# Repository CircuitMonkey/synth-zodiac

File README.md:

# synth-zodiac
Zodiac themed analog synthesizer, shaped like a Dodecahedron.

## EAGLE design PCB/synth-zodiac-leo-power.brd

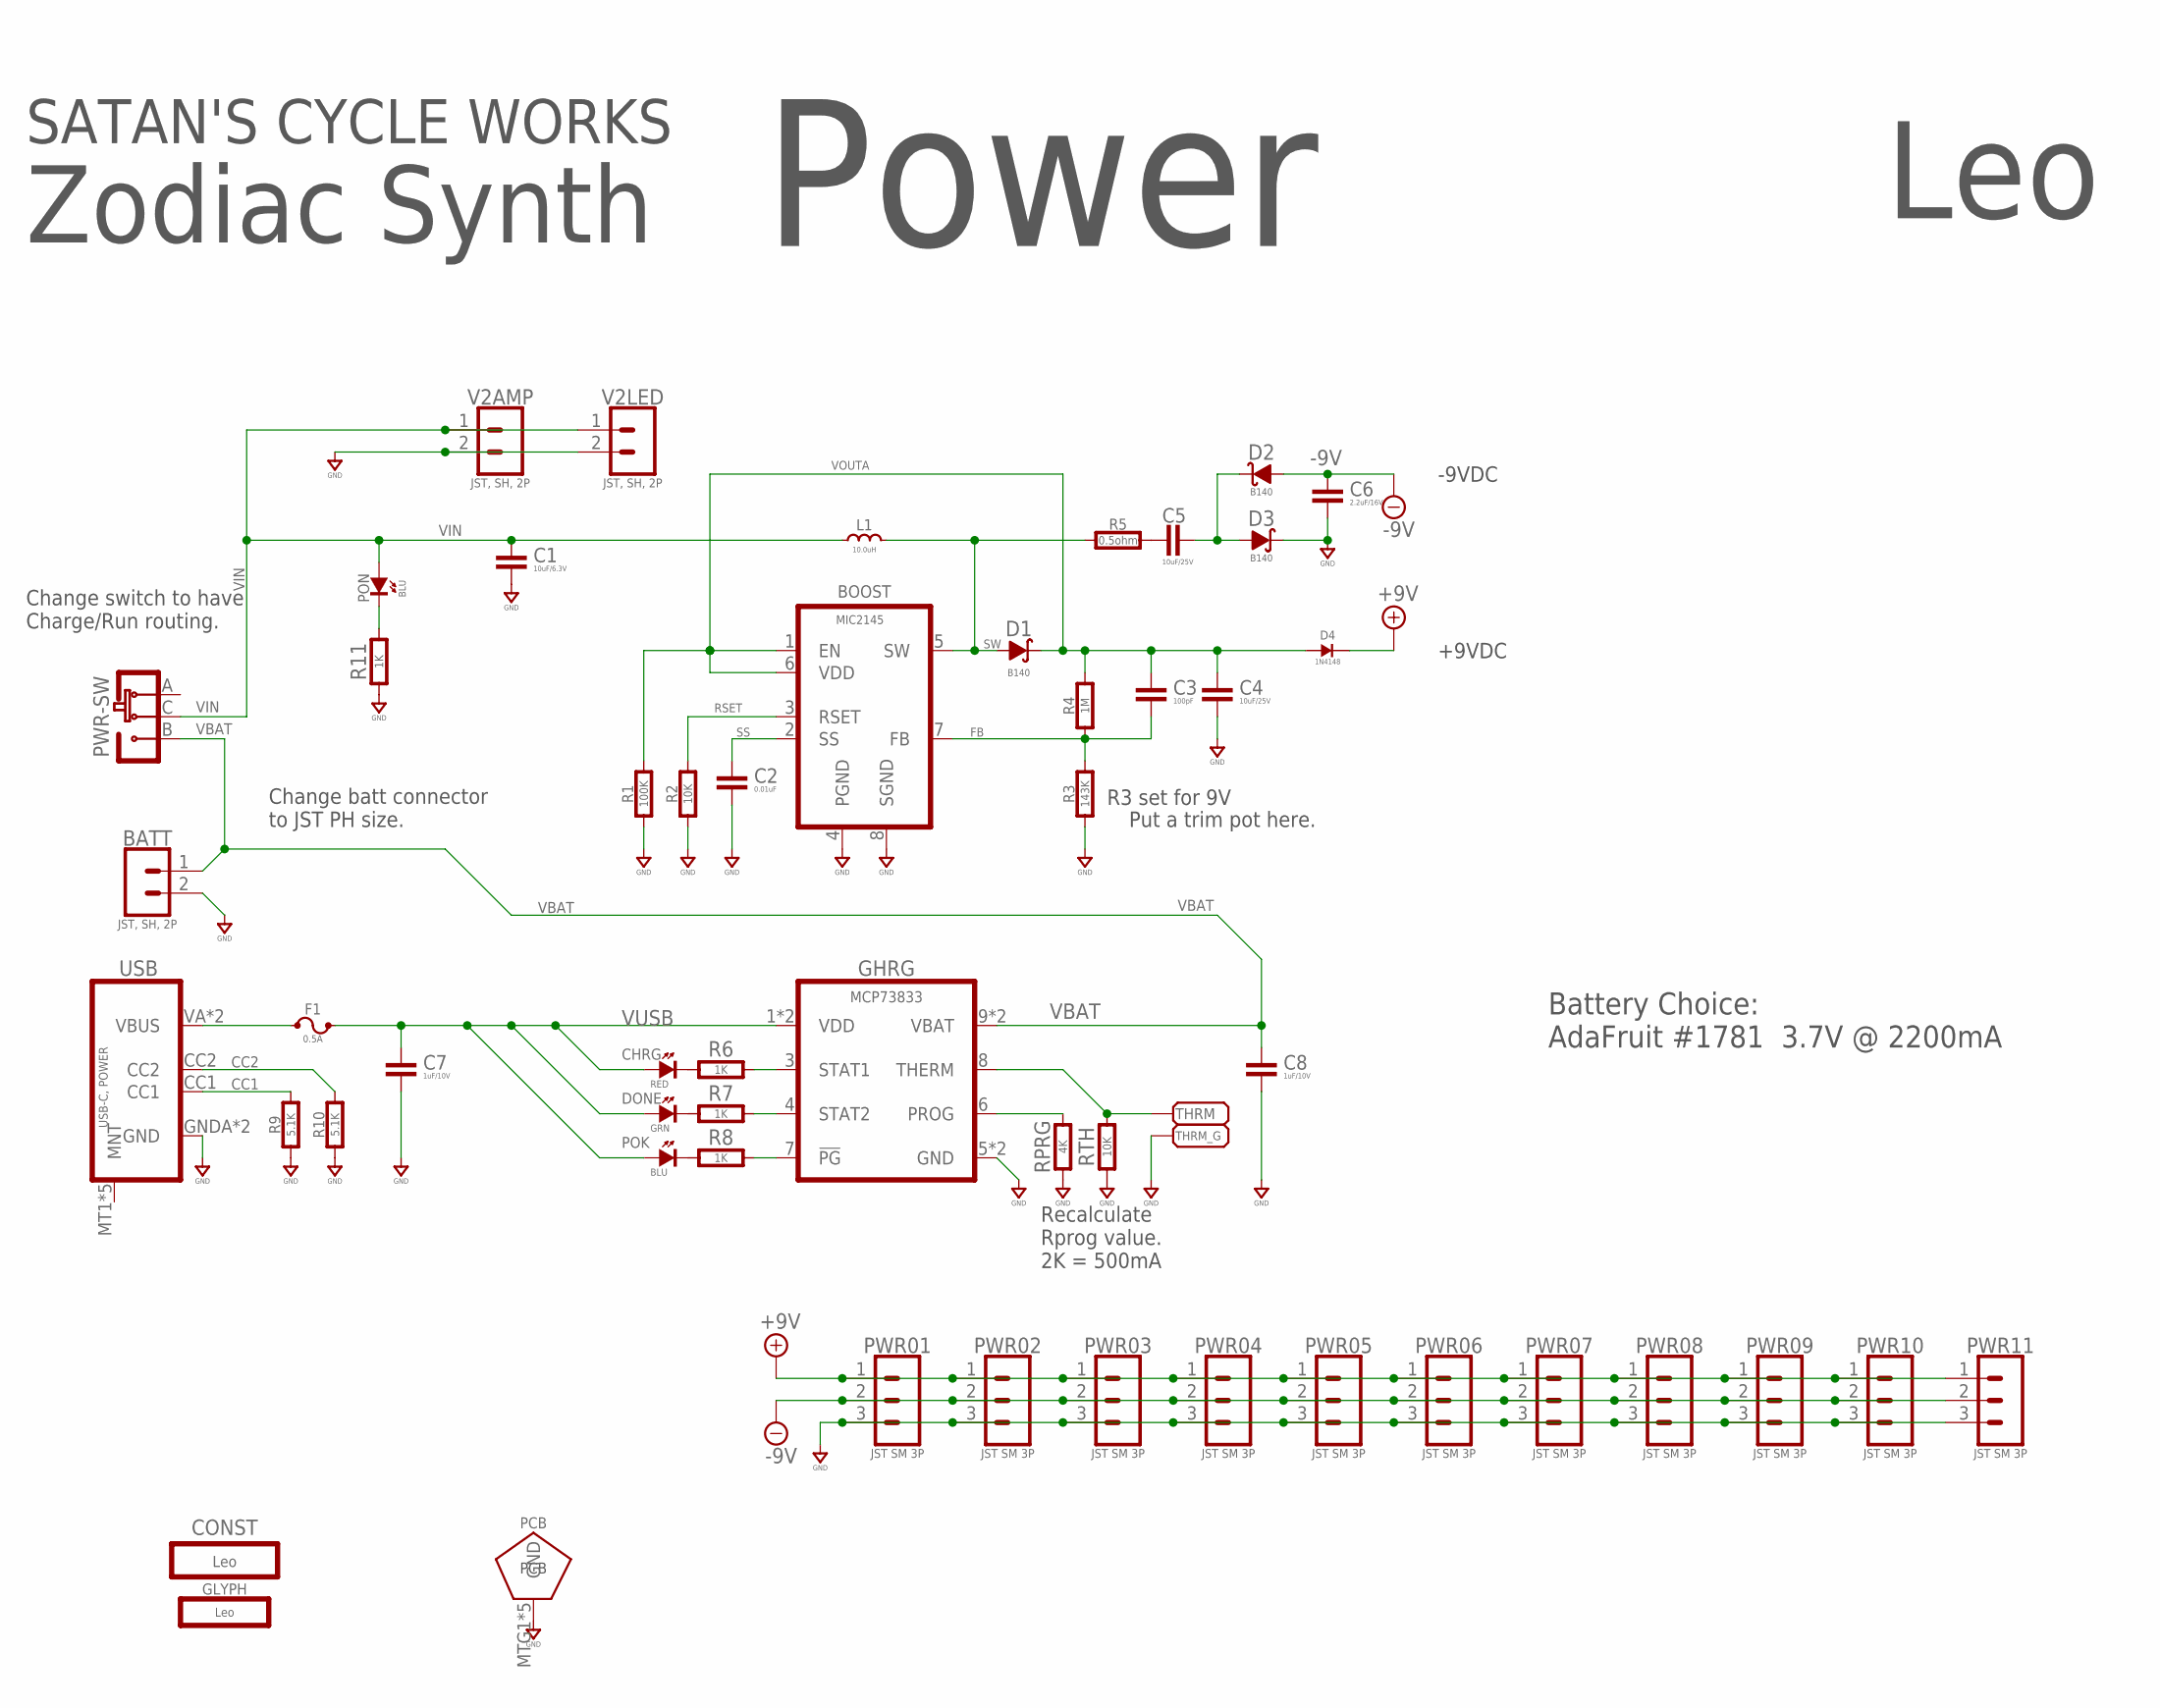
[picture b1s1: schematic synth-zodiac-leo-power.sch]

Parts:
BATT: JST, SH, 2P; BM02B-SRSS-TB
BOOST: MIC2145; MSOP8-0.65
C1: 10uF/6.3V; 0603-CAP
C2: 0.01uF; 0603-CAP
C3: 100pF; 0603-CAP
C4, C5: 10uF/25V; 0603-CAP
C6: 2.2uF/16V; 0603-CAP
C7, C8: 1uF/10V; 0603-CAP
CHRG: RED; SMD_0603
CONST: Leo; LEO-CONST
D1, D2, D3: B140; SMA
D4: 1N4148; SOD-123
DONE: GRN; SMD_0603
F1: 0.5A; BOURNS-MF-MSMF
GHRG: MCP73833; DFN-10-3X3
GLYPH: Leo; LEO-GLYPH
L1: 10.0uH; IND-SRN5040
PCB: PCB FAB; PENTAGON-40MM-RAD
POK: BLU; SMD_0603
PON: BLU; SMD_0603
PWR: SLIDE-SPDT-MNTSS-12-F45-TH-PCB-2; SS-12-F45-PNL-SMT-2
PWR01, PWR02, PWR03, PWR04, PWR05, PWR06, PWR07, PWR08, PWR09, PWR10, PWR11: JST SM 3P; BM03B-SRSS-TB
R1: 100K; 0603-RES
R2: 10K; 0603-RES
R3: 143K; 0603-RES
R4: 1M; 0603-RES
R5: 0.5ohm; 0603-RES
R6, R7, R8, R11: 1K; 0603-RES
R9, R10: 5.1K; 0603-RES
RPRG: 4K; 0603-RES
RTH: 10K; 0603-RES
THRM: PADSMD-050X050; SMD-050X050
THRM_G: PADSMD-050X050; SMD-050X050
USB: USB-C, POWER; GCT-USB4515-PANEL
V2AMP, V2LED: JST, SH, 2P; BM02B-SRSS-TB

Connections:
+9V: D4.K, PWR01.1, PWR02.1, PWR03.1, PWR04.1, PWR05.1, PWR06.1, PWR07.1, PWR08.1, PWR09.1, PWR10.1, PWR11.1
-9V: C6.1, D2.A, PWR01.2, PWR02.2, PWR03.2, PWR04.2, PWR05.2, PWR06.2, PWR07.2, PWR08.2, PWR09.2, PWR10.2, PWR11.2
CC1: R9.2, USB.CC1
CC2: R10.2, USB.CC2
FB: BOOST.7 (FB), C3.2, R3.2, R4.1
GND: BATT.2, BOOST.4 (PGND), BOOST.8 (SGND), C1.2, C2.2, C4.2, C6.2, C7.2, C8.2, D3.K, GHRG.5 (GND), GHRG.PAD (GND), PCB.MTG1, PCB.MTG2, PCB.MTG3, PCB.MTG4, PCB.MTG5, PWR01.3, PWR02.3, PWR03.3, PWR04.3, PWR05.3, PWR06.3, PWR07.3, PWR08.3, PWR09.3, PWR10.3, PWR11.3, R1.1, R2.1, R3.1, R9.1, R10.1, R11.1, RPRG.1, RTH.1, THRM_G.1, USB.GNDA (GND), USB.GNDB (GND), V2AMP.2, V2LED.2
unnamed: C5.1, R5.2
unnamed: C5.2, D2.K, D3.A
unnamed: CHRG.K (C), R6.1
unnamed: PON.K (C), R11.2
unnamed: DONE.K (C), R7.1
unnamed: POK.K (C), R8.1
unnamed: GHRG.6 (PROG), RPRG.2
unnamed: GHRG.3 (STAT1), R6.2
unnamed: GHRG.4 (STAT2), R7.2
unnamed: GHRG.7 (!PG), R8.2
unnamed: GHRG.8 (THERM), RTH.2, THRM.1
RSET: BOOST.3 (RSET), R2.2
SS: BOOST.2 (SS), C2.1
SW: BOOST.5 (SW), D1.A, L1.1, R5.1
VBAT: BATT.1, C8.1, GHRG.9 (VBAT), GHRG.10 (VBAT), PWR.B
VBUS: F1.1, USB.VA (VBUS), USB.VB (VBUS)
VIN: C1.1, L1.2, PON.A, PWR.C, V2AMP.1, V2LED.1
VOUTA: BOOST.1 (EN), BOOST.6 (VDD), C3.1, C4.1, D1.K, D4.A, R1.2, R4.2
VUSB: C7.1, CHRG.A, DONE.A, F1.2, GHRG.1 (VDD), GHRG.2 (VDD), POK.A

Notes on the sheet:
Battery Choice: AdaFruit #1781 3.7V @ 2200mA
R3 set for 9V
-9VDC
+9VDC
Put a trim pot here.
Recalculate Rprog value. 2K = 500mA
Power
Zodiac Synth
Leo
SATAN'S CYCLE WORKS
Change switch to have Charge/Run routing.
Change batt connector to JST PH size.

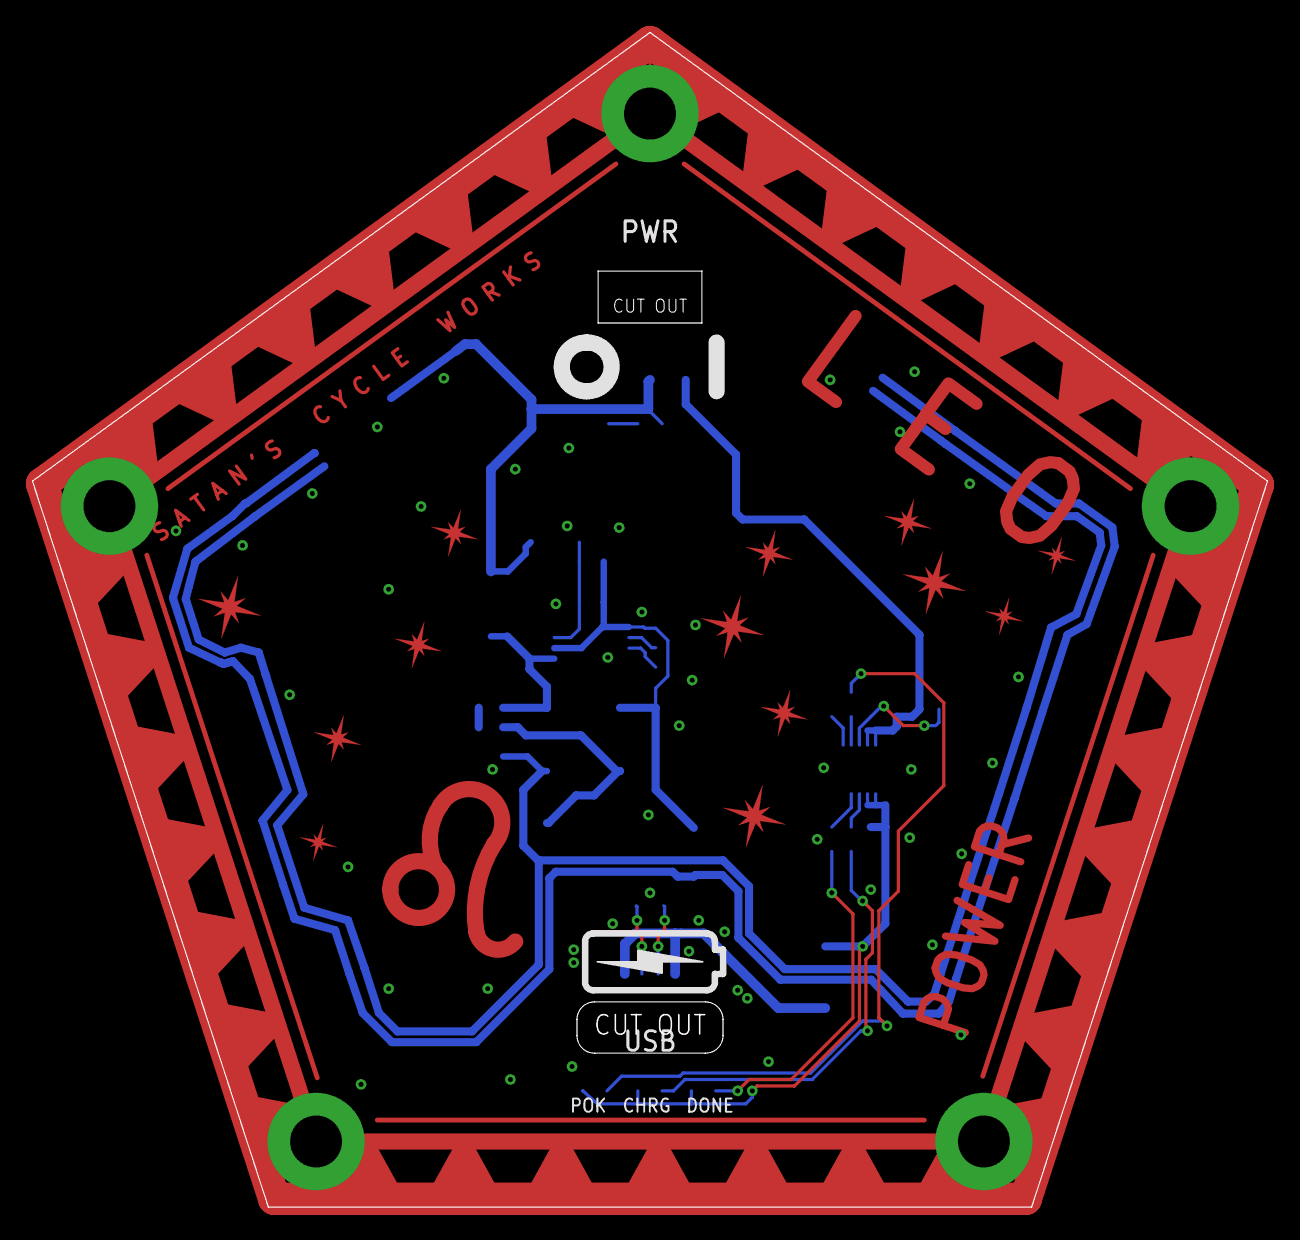
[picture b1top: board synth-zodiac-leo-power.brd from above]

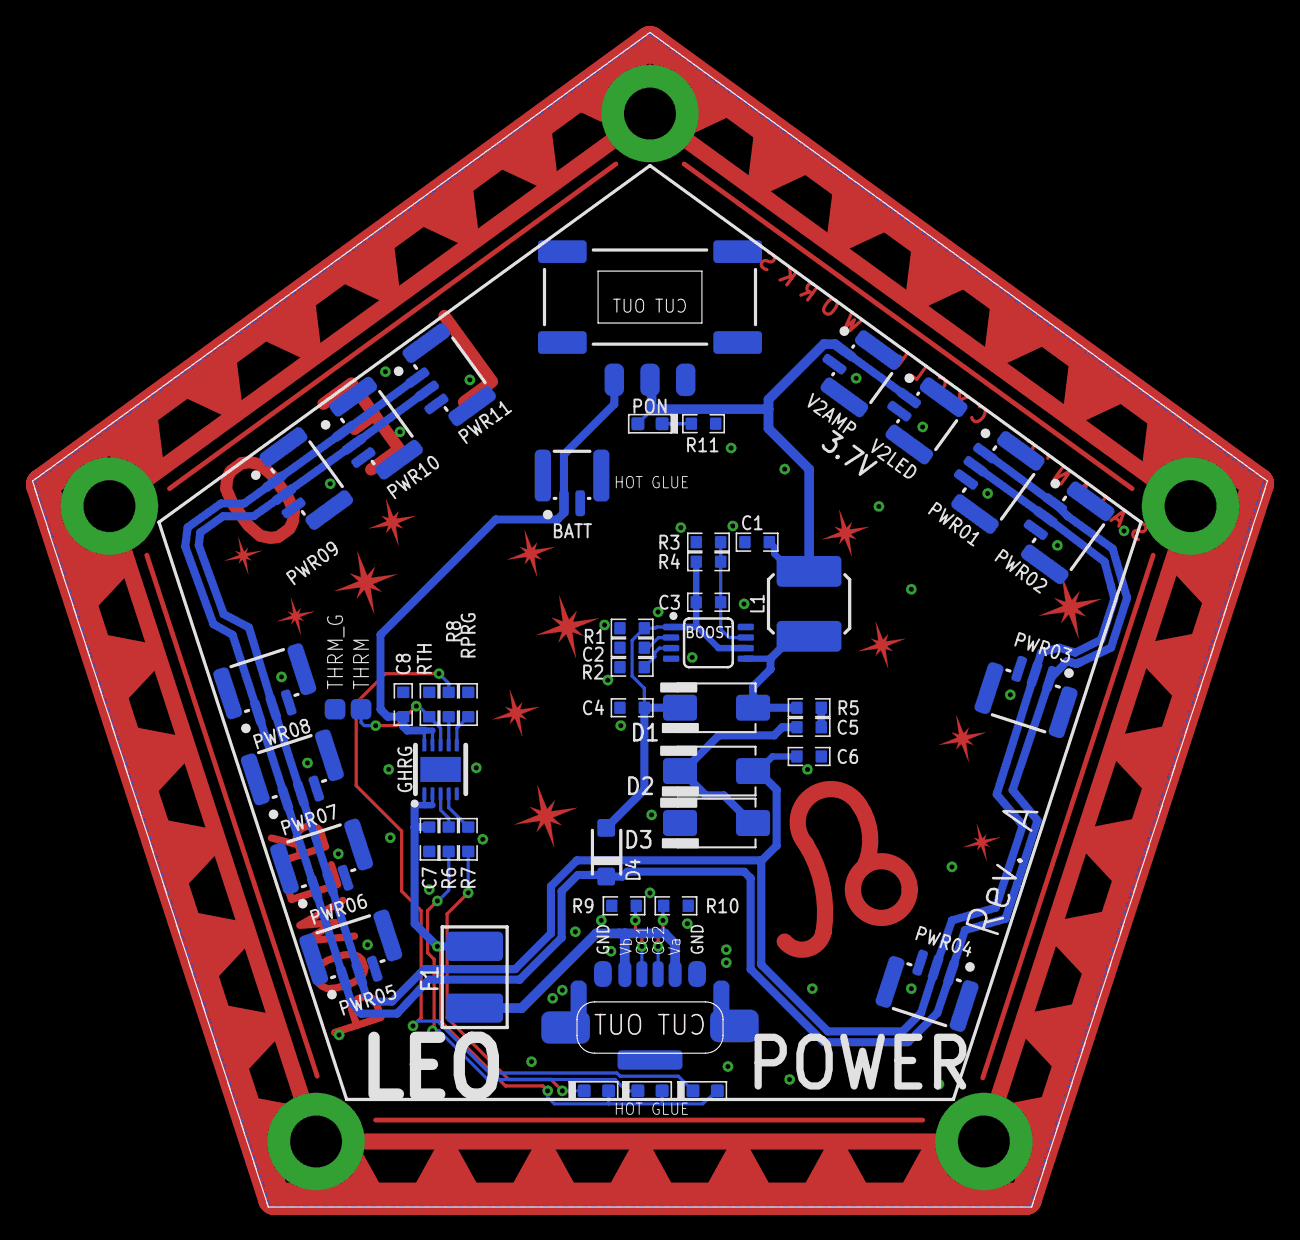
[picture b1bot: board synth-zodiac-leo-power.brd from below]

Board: 2 copper layers, 76.1 x 72.3 mm, 54 parts (49 on the bottom side), 25 nets.

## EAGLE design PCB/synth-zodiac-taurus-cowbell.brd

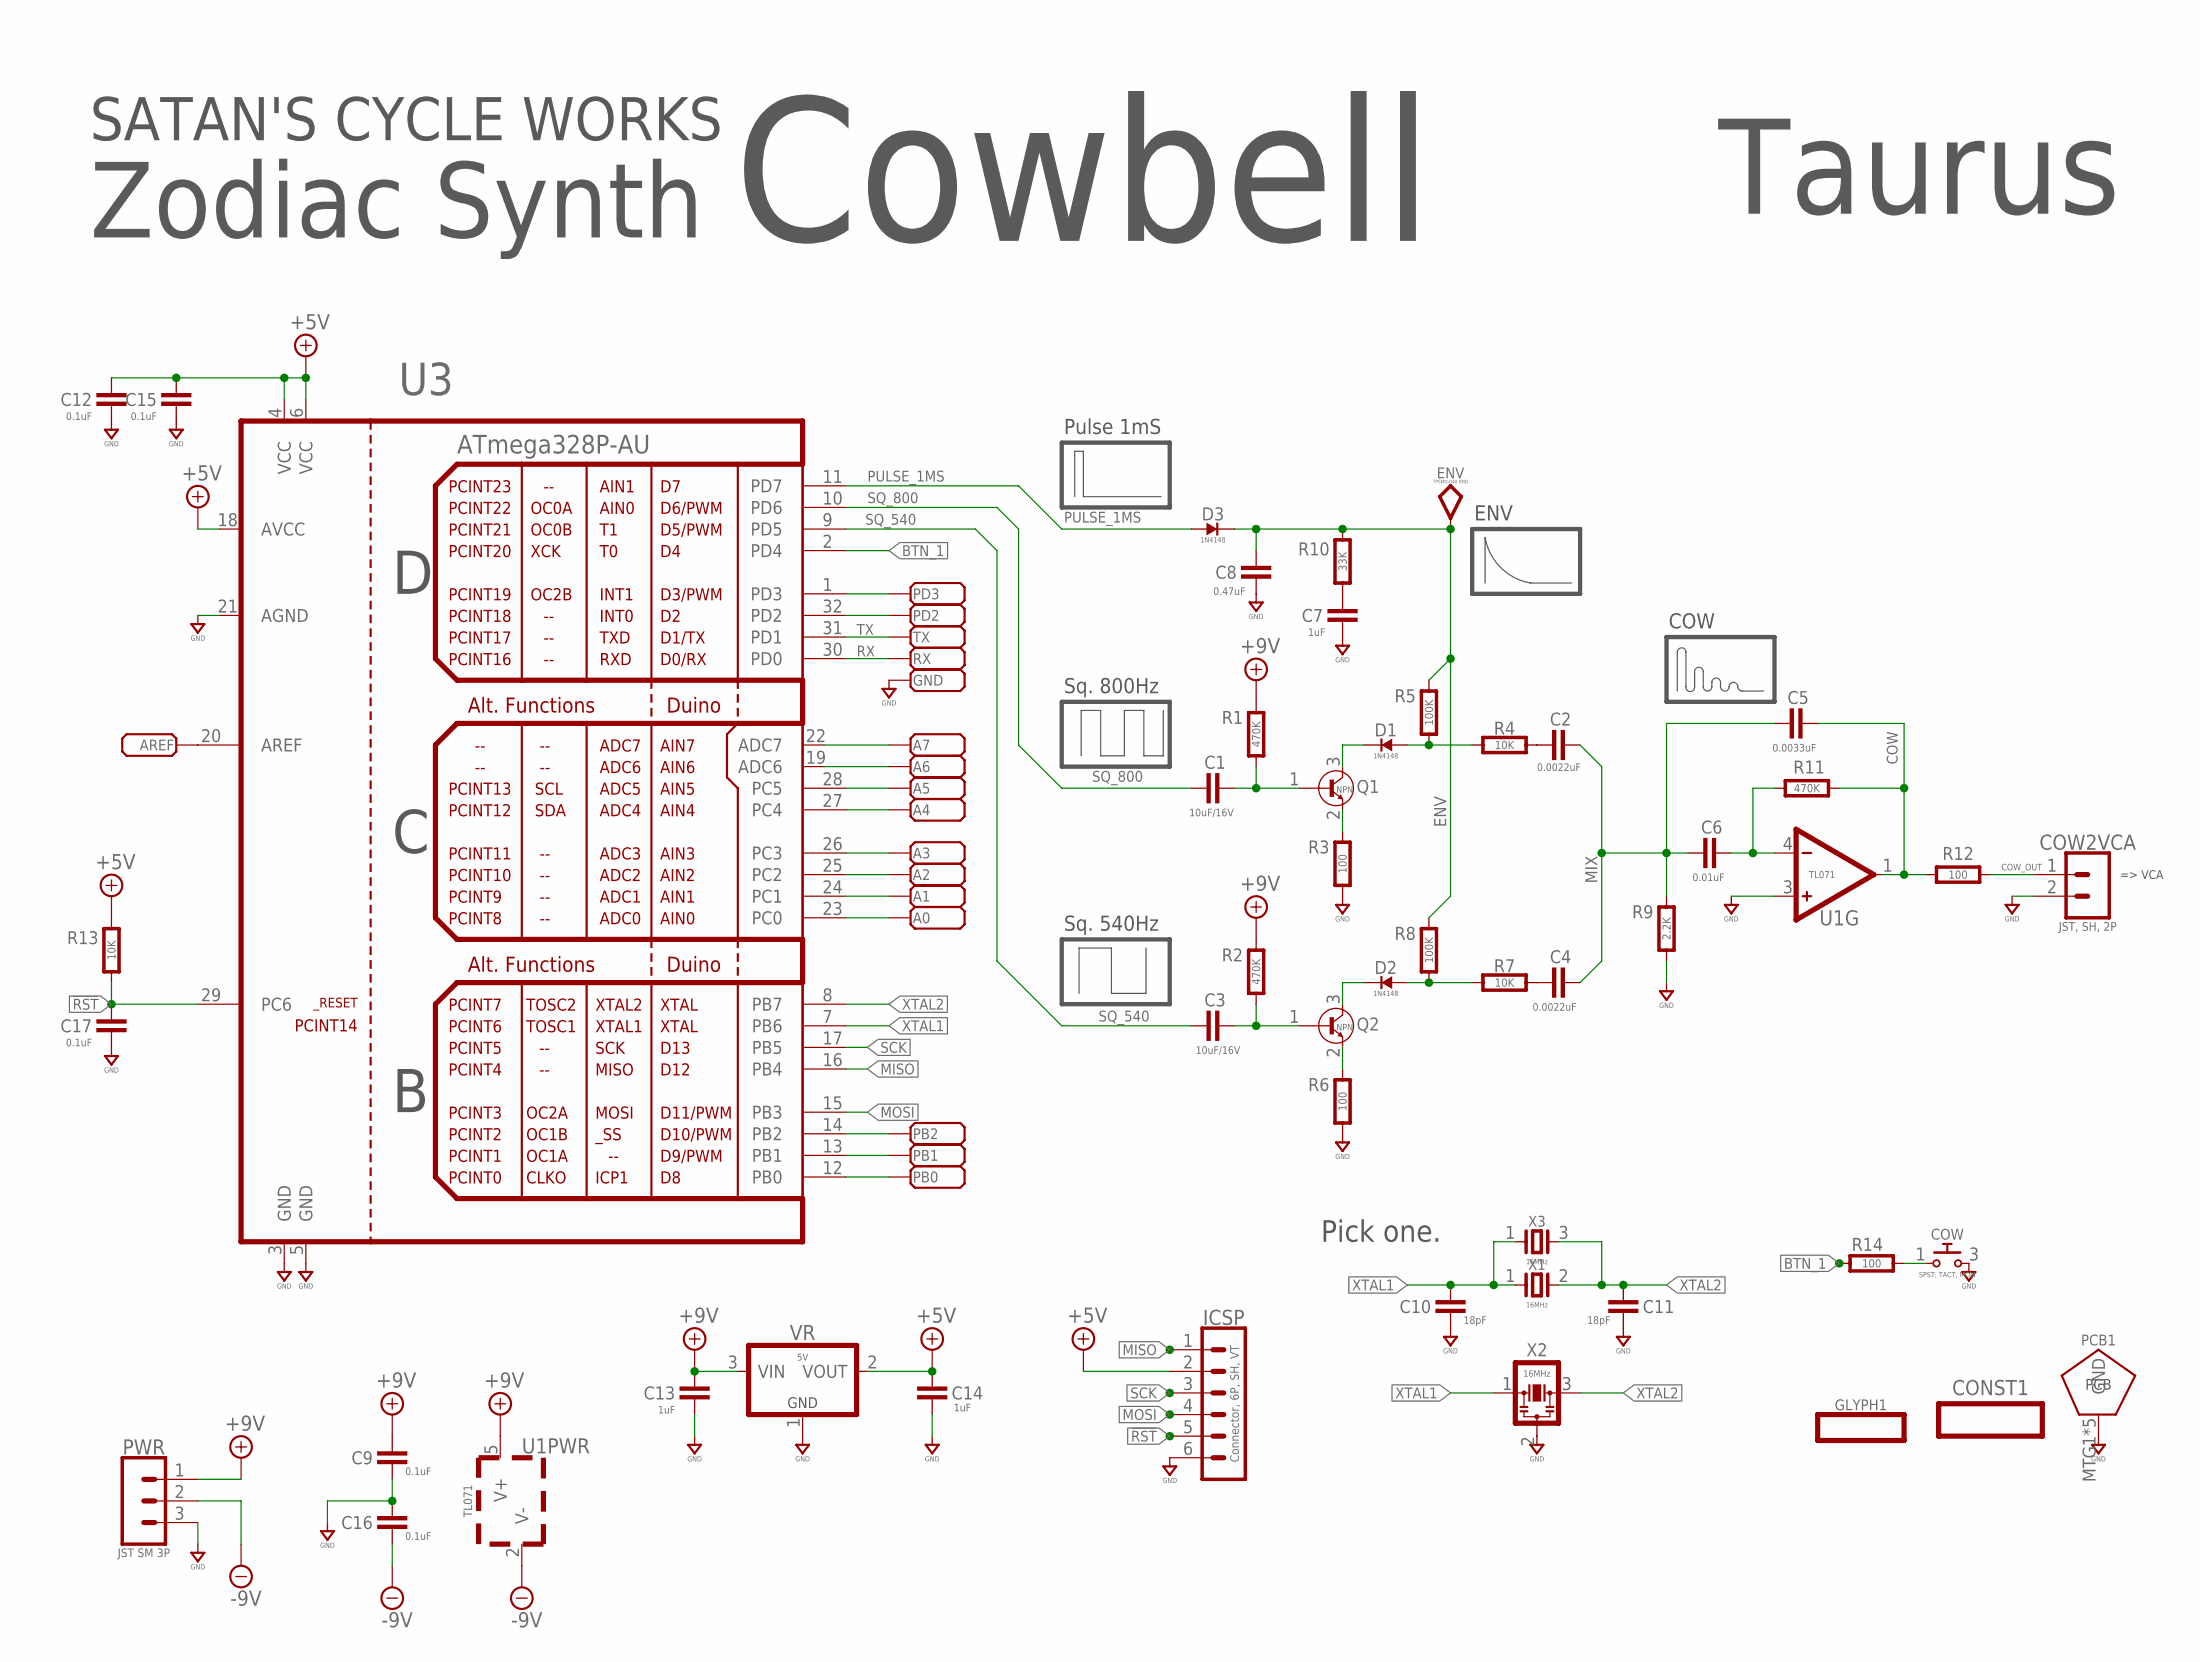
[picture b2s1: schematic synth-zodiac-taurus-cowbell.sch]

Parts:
A0, A1, A2, A3, A4, A5, A6, A7: PADSMD-050X050; SMD-050X050
AREF: PADSMD-050X050; SMD-050X050
C1, C3: 10uF/16V; 0603-CAP
C2, C4: 0.0022uF; 0603-CAP
C5: 0.0033uF; 0603-CAP
C6: 0.01uF; 0603-CAP
C7, C13, C14: 1uF; 0603-CAP
C8: 0.47uF; 0603-CAP
C9, C12, C15, C16, C17: 0.1uF; 0603-CAP
C10, C11: 18pF; 0603-CAP
CONST1: CONSTELLATION-TAURUS; TAURUS-CONST
COW: SPST, TACT, MOM; B3FS-BACKMOUNT
COW2VCA: JST, SH, 2P; BM02B-SRSS-TB
D1, D2, D3: 1N4148; SOD-123
ENV: TPSMD-040-RND; SMD-040MIL-RND
GLYPH1: GLYPH-TAURUS; TAURUS-GLYPH
GND: PADSMD-050X050; SMD-050X050
ICSP: Connector, 6P, SH, VT; BM06B-SRSS-TB
PB0, PB1, PB2: PADSMD-050X050; SMD-050X050
PCB1: PCB FAB; PENTAGON-40MM-RAD
PD2, PD3: PADSMD-050X050; SMD-050X050
PWR: JST SM 3P; BM03B-SRSS-TB
Q1, Q2: NPN; SOT-23
R1, R2, R11: 470K; 0603-RES
R3, R6, R12, R14: 100; 0603-RES
R4, R7, R13: 10K; 0603-RES
R5, R8: 100K; 0603-RES
R9: 2.2K; 0603-RES
R10: 33K; 0603-RES
RX: PADSMD-050X050; SMD-050X050
TX: PADSMD-050X050; SMD-050X050
U1: TL071; SOT-23-5
U3: ATmega328P-AU; TQFP-32-08
VR: 5V; SOT-23
X1: 16MHz; CTS_5X3
X2: 16MHz; CSTE-RESONATOR
X3: 16MHz; 32X25

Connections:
!RST: C17.1, ICSP.5, R13.2, U3.29 (PC6)
+5V: C12.1, C14.1, C15.1, ICSP.2, R13.1, U3.4 (VCC), U3.6 (VCC), U3.18 (AVCC), VR.2 (VOUT)
+9V: C9.1, C13.1, PWR.1, R1.2, R2.2, U1.5 (V+), VR.3 (VIN)
-9V: C16.2, PWR.2, U1.2 (V-)
BTN_1: R14.1, U3.2 (PD4)
COW: C5.2, R11.2, R12.1, U1.1 (OUT)
COW_OUT: COW2VCA.1, R12.2
ENV: C8.1, D3.K, ENV.TP, R5.2, R8.2, R10.1
GND: C7.2, C8.2, C9.2, C10.2, C11.2, C12.2, C13.2, C14.2, C15.2, C16.1, C17.2, COW.3 (2), COW2VCA.2, GND.1, ICSP.6, PCB1.MTG1, PCB1.MTG2, PCB1.MTG3, PCB1.MTG4, PCB1.MTG5, PWR.3, R3.1, R6.1, R9.1, U1.3 (+), U3.3 (GND), U3.5 (GND), U3.21 (AGND), VR.1 (GND), X2.2
MISO: ICSP.1, U3.16 (PB4)
MIX: C2.2, C4.2, C5.1, C6.1, R9.2
MOSI: ICSP.4, U3.15 (PB3)
unnamed: D1.K, Q1.3 (COLLECTOR)
unnamed: Q1.2 (EMITTER), R3.2
unnamed: C1.2, Q1.1 (BASE), R1.1
unnamed: D1.A, R4.1, R5.1
unnamed: C2.1, R4.2
unnamed: D2.K, Q2.3 (COLLECTOR)
unnamed: Q2.2 (EMITTER), R6.2
unnamed: C3.2, Q2.1 (BASE), R2.1
unnamed: D2.A, R7.1, R8.1
unnamed: C4.1, R7.2
unnamed: COW.1, R14.2
unnamed: PD3.1, U3.1 (PD3)
unnamed: C6.2, R11.1, U1.4 (-)
unnamed: PD2.1, U3.32 (PD2)
unnamed: C7.1, R10.2
unnamed: PB2.1, U3.14 (PB2)
unnamed: PB1.1, U3.13 (PB1)
unnamed: PB0.1, U3.12 (PB0)
unnamed: A0.1, U3.23 (PC0)
unnamed: A1.1, U3.24 (PC1)
unnamed: A2.1, U3.25 (PC2)
unnamed: A3.1, U3.26 (PC3)
unnamed: A4.1, U3.27 (PC4)
unnamed: A5.1, U3.28 (PC5)
unnamed: A6.1, U3.19 (ADC6)
unnamed: A7.1, U3.22 (ADC7)
unnamed: AREF.1, U3.20 (AREF)
PULSE_1MS: D3.A, U3.11 (PD7)
RX: RX.1, U3.30 (PD0)
SCK: ICSP.3, U3.17 (PB5)
SQ_540: C3.1, U3.9 (PD5)
SQ_800: C1.1, U3.10 (PD6)
TX: TX.1, U3.31 (PD1)
XTAL1: C10.1, U3.7 (PB6), X1.1, X2.1, X3.1
XTAL2: C11.1, U3.8 (PB7), X1.2, X2.3, X3.3

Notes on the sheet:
=> VCA
ENV
Pulse 1mS
Pick one.
Sq. 800Hz
Sq. 540Hz
COW
Cowbell
Zodiac Synth
Taurus
SATAN'S CYCLE WORKS

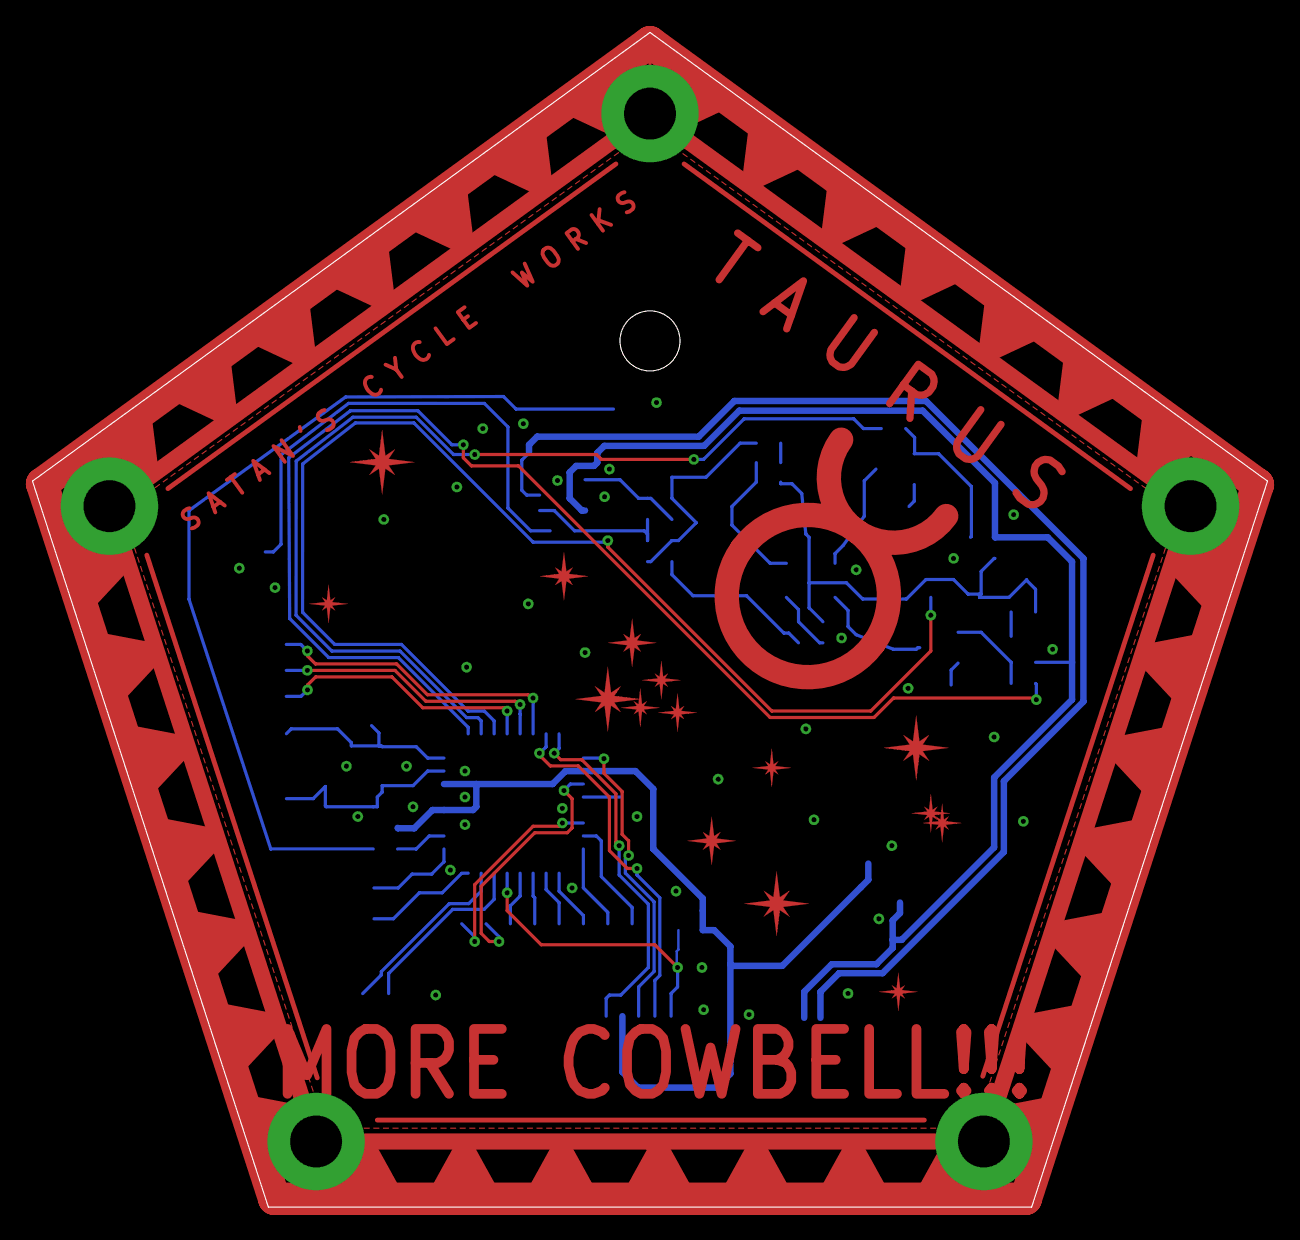
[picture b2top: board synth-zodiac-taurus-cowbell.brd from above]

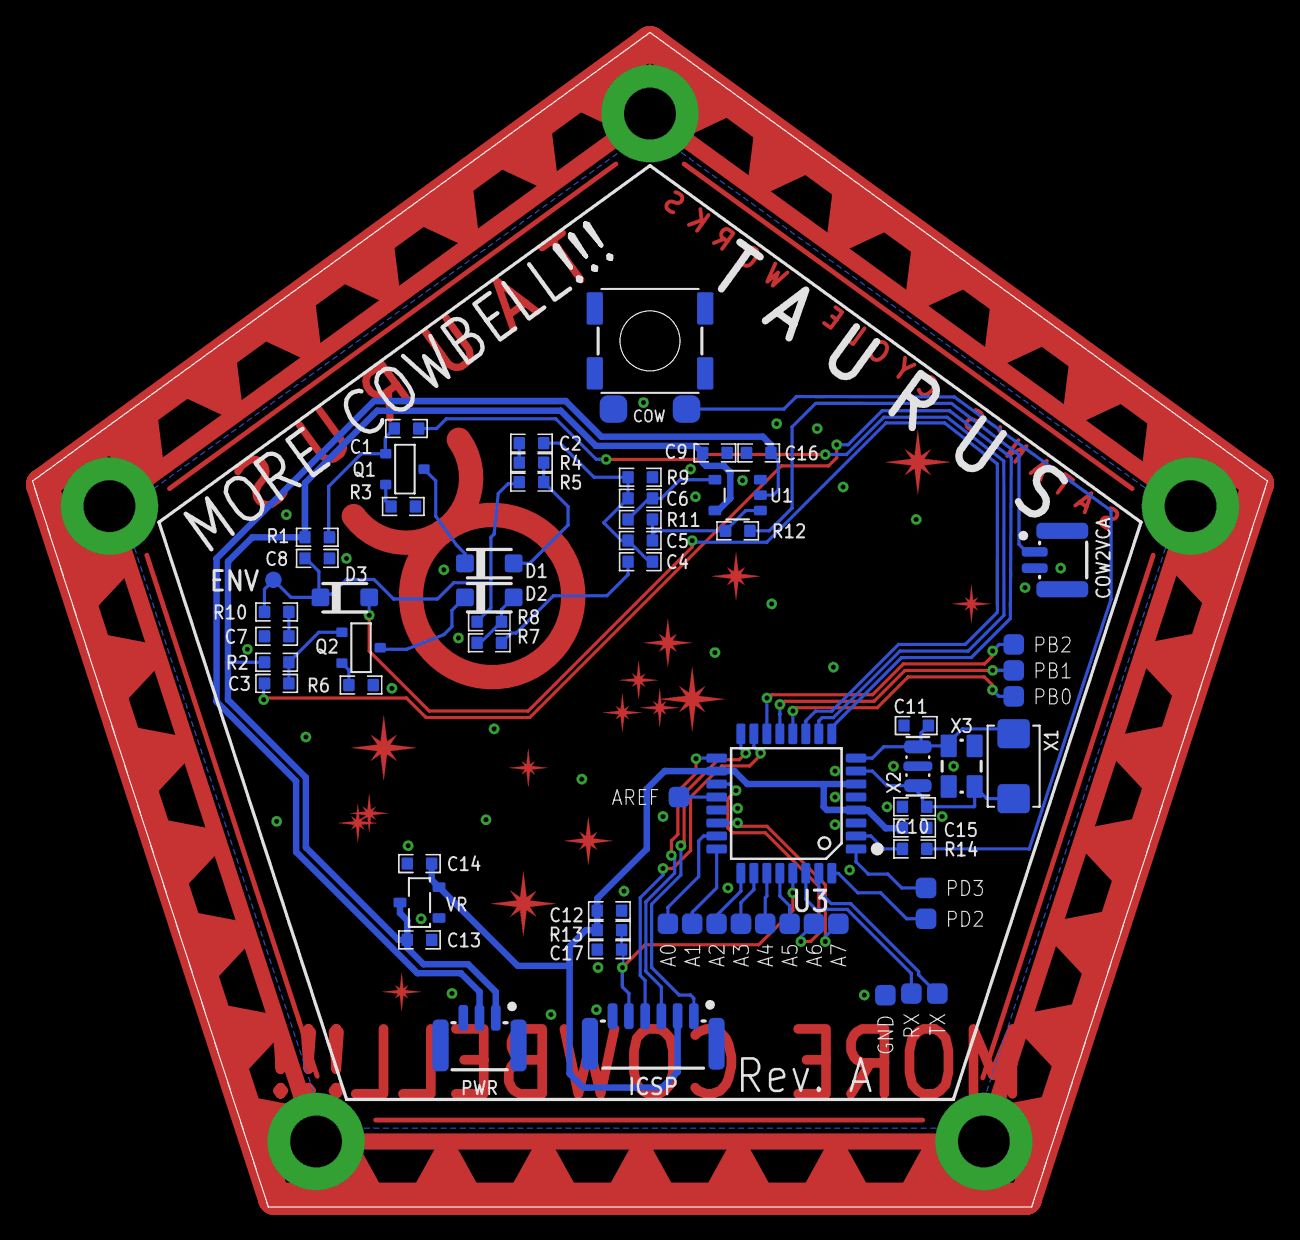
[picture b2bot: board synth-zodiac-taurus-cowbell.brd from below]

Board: 2 copper layers, 76.1 x 72.4 mm, 67 parts (63 on the bottom side), 47 nets.

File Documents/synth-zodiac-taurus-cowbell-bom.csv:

"Part";"Value";"Device";"Package";"Description";"COST01";"COST10";"COST100";"MFR";"MOUSER";"MPN";"MPN2";"OC_MOUSER";"OC_SEEED";"VALUE";
"A0";"PADSMD-050X050";"PADSMD-050X050";"SMD-050X050";"Solder Pad";"";"";"";"";"";"";"";"";"";"";
"A1";"PADSMD-050X050";"PADSMD-050X050";"SMD-050X050";"Solder Pad";"";"";"";"";"";"";"";"";"";"";
"A2";"PADSMD-050X050";"PADSMD-050X050";"SMD-050X050";"Solder Pad";"";"";"";"";"";"";"";"";"";"";
"A3";"PADSMD-050X050";"PADSMD-050X050";"SMD-050X050";"Solder Pad";"";"";"";"";"";"";"";"";"";"";
"A4";"PADSMD-050X050";"PADSMD-050X050";"SMD-050X050";"Solder Pad";"";"";"";"";"";"";"";"";"";"";
"A5";"PADSMD-050X050";"PADSMD-050X050";"SMD-050X050";"Solder Pad";"";"";"";"";"";"";"";"";"";"";
"A6";"PADSMD-050X050";"PADSMD-050X050";"SMD-050X050";"Solder Pad";"";"";"";"";"";"";"";"";"";"";
"A7";"PADSMD-050X050";"PADSMD-050X050";"SMD-050X050";"Solder Pad";"";"";"";"";"";"";"";"";"";"";
"AREF";"PADSMD-050X050";"PADSMD-050X050";"SMD-050X050";"Solder Pad";"";"";"";"";"";"";"";"";"";"";
"C1";"10uF/16V";"CAPACITOR0603";"0603-CAP";"Capacitor";"0.12";"0.09";"0.05";"";"";"";"";"";"";"";
"C2";"0.0022uF";"CAPACITOR0603";"0603-CAP";"Capacitor";"0.12";"0.09";"0.05";"";"";"";"";"";"";"";
"C3";"10uF/16V";"CAPACITOR0603";"0603-CAP";"Capacitor";"0.12";"0.09";"0.05";"";"";"";"";"";"";"";
"C4";"0.0022uF";"CAPACITOR0603";"0603-CAP";"Capacitor";"0.12";"0.09";"0.05";"";"";"";"";"";"";"";
"C5";"0.0033uF";"CAPACITOR0603";"0603-CAP";"Capacitor";"0.12";"0.09";"0.05";"";"";"";"";"";"";"";
"C6";"0.01uF";"CAPACITOR0603";"0603-CAP";"Capacitor";"0.12";"0.09";"0.05";"";"";"";"";"";"";"";
"C7";"1uF";"CAPACITOR0603";"0603-CAP";"Capacitor";"0.12";"0.09";"0.05";"";"";"";"";"";"";"";
"C8";"0.47uF";"CAPACITOR0603";"0603-CAP";"Capacitor";"0.12";"0.09";"0.05";"";"";"";"";"";"";"";
"C9";"0.1uF";"CAPACITOR0603";"0603-CAP";"Capacitor";"0.12";"0.09";"0.05";"";"";"";"";"";"";"";
"C10";"18pF";"CAPACITOR0603";"0603-CAP";"Capacitor";"0.12";"0.09";"0.05";"";"";"";"";"";"";"";
"C11";"18pF";"CAPACITOR0603";"0603-CAP";"Capacitor";"0.12";"0.09";"0.05";"";"";"";"";"";"";"";
"C12";"0.1uF";"CAPACITOR0603";"0603-CAP";"Capacitor";"0.12";"0.09";"0.05";"";"";"";"";"";"";"";
"C13";"1uF";"CAPACITOR0603";"0603-CAP";"Capacitor";"0.12";"0.09";"0.05";"";"";"";"";"";"";"";
"C14";"1uF";"CAPACITOR0603";"0603-CAP";"Capacitor";"0.12";"0.09";"0.05";"";"";"";"";"";"";"";
"C15";"0.1uF";"CAPACITOR0603";"0603-CAP";"Capacitor";"0.12";"0.09";"0.05";"";"";"";"";"";"";"";
"C16";"0.1uF";"CAPACITOR0603";"0603-CAP";"Capacitor";"0.12";"0.09";"0.05";"";"";"";"";"";"";"";
"C17";"0.1uF";"CAPACITOR0603";"0603-CAP";"Capacitor";"0.12";"0.09";"0.05";"";"";"";"";"";"";"";
"CONST1";"";"CONSTELLATION-TAURUS";"TAURUS-CONST";"Constellations";"";"";"";"";"";"";"";"";"";"";
"COW";"SPST, TACT, MOM";"PUSHBTN-MOMB3FS-BLIND";"B3FS-BACKMOUNT";"Pushbutton Switch";"0.15";"0.12";"0.09";"CK";"";"B3FS";"Tayda A-3961(2.3mm), A-5134(3.14mm,RA)";"";"";"SPST, TACT, MOM";
"COW2VCA";"JST, SH, 2P";"02P-SM-VT-SMT";"BM02B-SRSS-TB";"2 pin connector";"0.45";"0.4";"0.35";"JST";"";"BMB02B-SRSS-TB";"";"";"";"JST, SH, 2P";
"D1";"1N4148";"DIODE-1N4148";"SOD-123";"Diode";"0.20";"0.18";"0.10";"";"";"1N4148W";"";"";"";"1N4148";
"D2";"1N4148";"DIODE-1N4148";"SOD-123";"Diode";"0.20";"0.18";"0.10";"";"";"1N4148W";"";"";"";"1N4148";
"D3";"1N4148";"DIODE-1N4148";"SOD-123";"Diode";"0.20";"0.18";"0.10";"";"";"1N4148W";"";"";"";"1N4148";
"ENV";"TPSMD-040-RND";"TPSMD-040-RND";"SMD-040MIL-RND";"Test Point -- Testpoint";"";"";"";"";"";"";"";"";"";"";
"GLYPH1";"";"GLYPH-TAURUS";"TAURUS-GLYPH";"Glyph";"";"";"";"";"";"";"";"";"";"";
"GND";"PADSMD-050X050";"PADSMD-050X050";"SMD-050X050";"Solder Pad";"";"";"";"";"";"";"";"";"";"";
"ICSP";"Connector, 6P, SH, VT";"06P-SM-VT-SMT";"BM06B-SRSS-TB";"Connector, 6P";"0.60";"0.52";"0.49";"JST";"";"BM06-SRSS-TB";"";"";"";"Connector, 6P, SM, VT";
"PB0";"PADSMD-050X050";"PADSMD-050X050";"SMD-050X050";"Solder Pad";"";"";"";"";"";"";"";"";"";"";
"PB1";"PADSMD-050X050";"PADSMD-050X050";"SMD-050X050";"Solder Pad";"";"";"";"";"";"";"";"";"";"";
"PB2";"PADSMD-050X050";"PADSMD-050X050";"SMD-050X050";"Solder Pad";"";"";"";"";"";"";"";"";"";"";
"PCB1";"PCB FAB";"PENTAGON-40R";"PENTAGON-40MM-RAD";"Pentagram shaped PCB";"";"";"";"";"";"";"";"";"";"PCB FAB";
"PD2";"PADSMD-050X050";"PADSMD-050X050";"SMD-050X050";"Solder Pad";"";"";"";"";"";"";"";"";"";"";
"PD3";"PADSMD-050X050";"PADSMD-050X050";"SMD-050X050";"Solder Pad";"";"";"";"";"";"";"";"";"";"";
"PWR";"JST SM 3P";"03P-SM-VT-SMT";"BM03B-SRSS-TB";"3 pin connector";"0.60";"0.45";"0.38";"JST";"";"BM03B-SRSS-TB";"";"";"";"JST SM 3P";
"Q1";"NPN";"NPN-BC846";"SOT-23";"NPN BJ Transistor";"0.20";"0.16";"0.10";"On Semiconductor";"https://www.mouser.com/ProductDetail/ON-Semiconductor/BC846BLT1G";"BC846";"";"";"";"NPN";
"Q2";"NPN";"NPN-BC846";"SOT-23";"NPN BJ Transistor";"0.20";"0.16";"0.10";"On Semiconductor";"https://www.mouser.com/ProductDetail/ON-Semiconductor/BC846BLT1G";"BC846";"";"";"";"NPN";
"R1";"470K";"RESISTOR0603";"0603-RES";"Resistor";"0.10";"0.05";"0.02";"";"";"";"";"";"";"";
"R2";"470K";"RESISTOR0603";"0603-RES";"Resistor";"0.10";"0.05";"0.02";"";"";"";"";"";"";"";
"R3";"100";"RESISTOR0603";"0603-RES";"Resistor";"0.10";"0.05";"0.02";"";"";"";"";"";"";"";
"R4";"10K";"RESISTOR0603";"0603-RES";"Resistor";"0.10";"0.05";"0.02";"";"";"";"";"";"";"";
"R5";"100K";"RESISTOR0603";"0603-RES";"Resistor";"0.10";"0.05";"0.02";"";"";"";"";"";"";"";
"R6";"100";"RESISTOR0603";"0603-RES";"Resistor";"0.10";"0.05";"0.02";"";"";"";"";"";"";"";
"R7";"10K";"RESISTOR0603";"0603-RES";"Resistor";"0.10";"0.05";"0.02";"";"";"";"";"";"";"";
"R8";"100K";"RESISTOR0603";"0603-RES";"Resistor";"0.10";"0.05";"0.02";"";"";"";"";"";"";"";
"R9";"2.2K";"RESISTOR0603";"0603-RES";"Resistor";"0.10";"0.05";"0.02";"";"";"";"";"";"";"";
"R10";"33K";"RESISTOR0603";"0603-RES";"Resistor";"0.10";"0.05";"0.02";"";"";"";"";"";"";"";
"R11";"470K";"RESISTOR0603";"0603-RES";"Resistor";"0.10";"0.05";"0.02";"";"";"";"";"";"";"";
"R12";"100";"RESISTOR0603";"0603-RES";"Resistor";"0.10";"0.05";"0.02";"";"";"";"";"";"";"";
"R13";"33K";"RESISTOR0603";"0603-RES";"Resistor";"0.10";"0.05";"0.02";"";"";"";"";"";"";"";
"R14";"100";"RESISTOR0603";"0603-RES";"Resistor";"0.10";"0.05";"0.02";"";"";"";"";"";"";"";
"RX";"PADSMD-050X050";"PADSMD-050X050";"SMD-050X050";"Solder Pad";"";"";"";"";"";"";"";"";"";"";
"TX";"PADSMD-050X050";"PADSMD-050X050";"SMD-050X050";"Solder Pad";"";"";"";"";"";"";"";"";"";"";
"U1";"TL071";"SINGLE-TL071";"SOT-23-5";"Single channel Op-amp";"0.46";"0.37";"0.29";"TI";"";"TL071HIDBV";"";"";"";"TL071";
"U3";"ATmega328P-AU";"ATMEGA328AU";"TQFP-32-08";"Atmega 328P";"";"";"";"Atmel";"";"ATMEGA328P-AU";"";"556-ATMEGA328P-AU";"310010049";"ATmega328P-AU";
"VR";"5V";"LDO-3P--5V-SOT23";"SOT-23";"regulator 3-pin";"0.66";"0.56";"0.39";"Diodes, Inc.";"";"AP7387-50SA";"";"";"";"5V";
"X1";"16MHz";"2PCTS_445";"CTS_5X3";"Crystal";"0.65";"0.55";"0.45";"CTS";"";"445C35K16M0000";"";"";"";"16MHz";
"X2";"16MHz";"RESONATOR-CSTE16";"CSTE-RESONATOR";"Resonator";"0.35";"0.30";"0.27";"Murata";"";"CSTCE16M";"";"";"";"16MHz";
"X3";"16MHz";"2P3.2X2.5";"32X25";"Crystal";"";"";"";"Epson";"";"FA-238 16.0000MB-K3";"";"";"";"16MHz";
